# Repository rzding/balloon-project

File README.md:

# SSI high-altitude balloon project

**Firmware:** [`balloon-project-stm32mx/`](balloon-project-stm32mx/) — STM32F411 flight-computer firmware (build, flash, and coding standards).

**Standards and phases:** [`Software Documents/Main Developmental Roadmap.md`](Software%20Documents/Main%20Developmental%20Roadmap.md)

**Verification workflow:** [`Software Documents/Firmware Development Guidelines.md`](Software%20Documents/Firmware%20Development%20Guidelines.md) — deferred hardware, host tests, bench backlog (roadmap §21). Software-complete unblocks the next driver phase; hardware exit is ticked during bring-up week, not before coding the next phase.

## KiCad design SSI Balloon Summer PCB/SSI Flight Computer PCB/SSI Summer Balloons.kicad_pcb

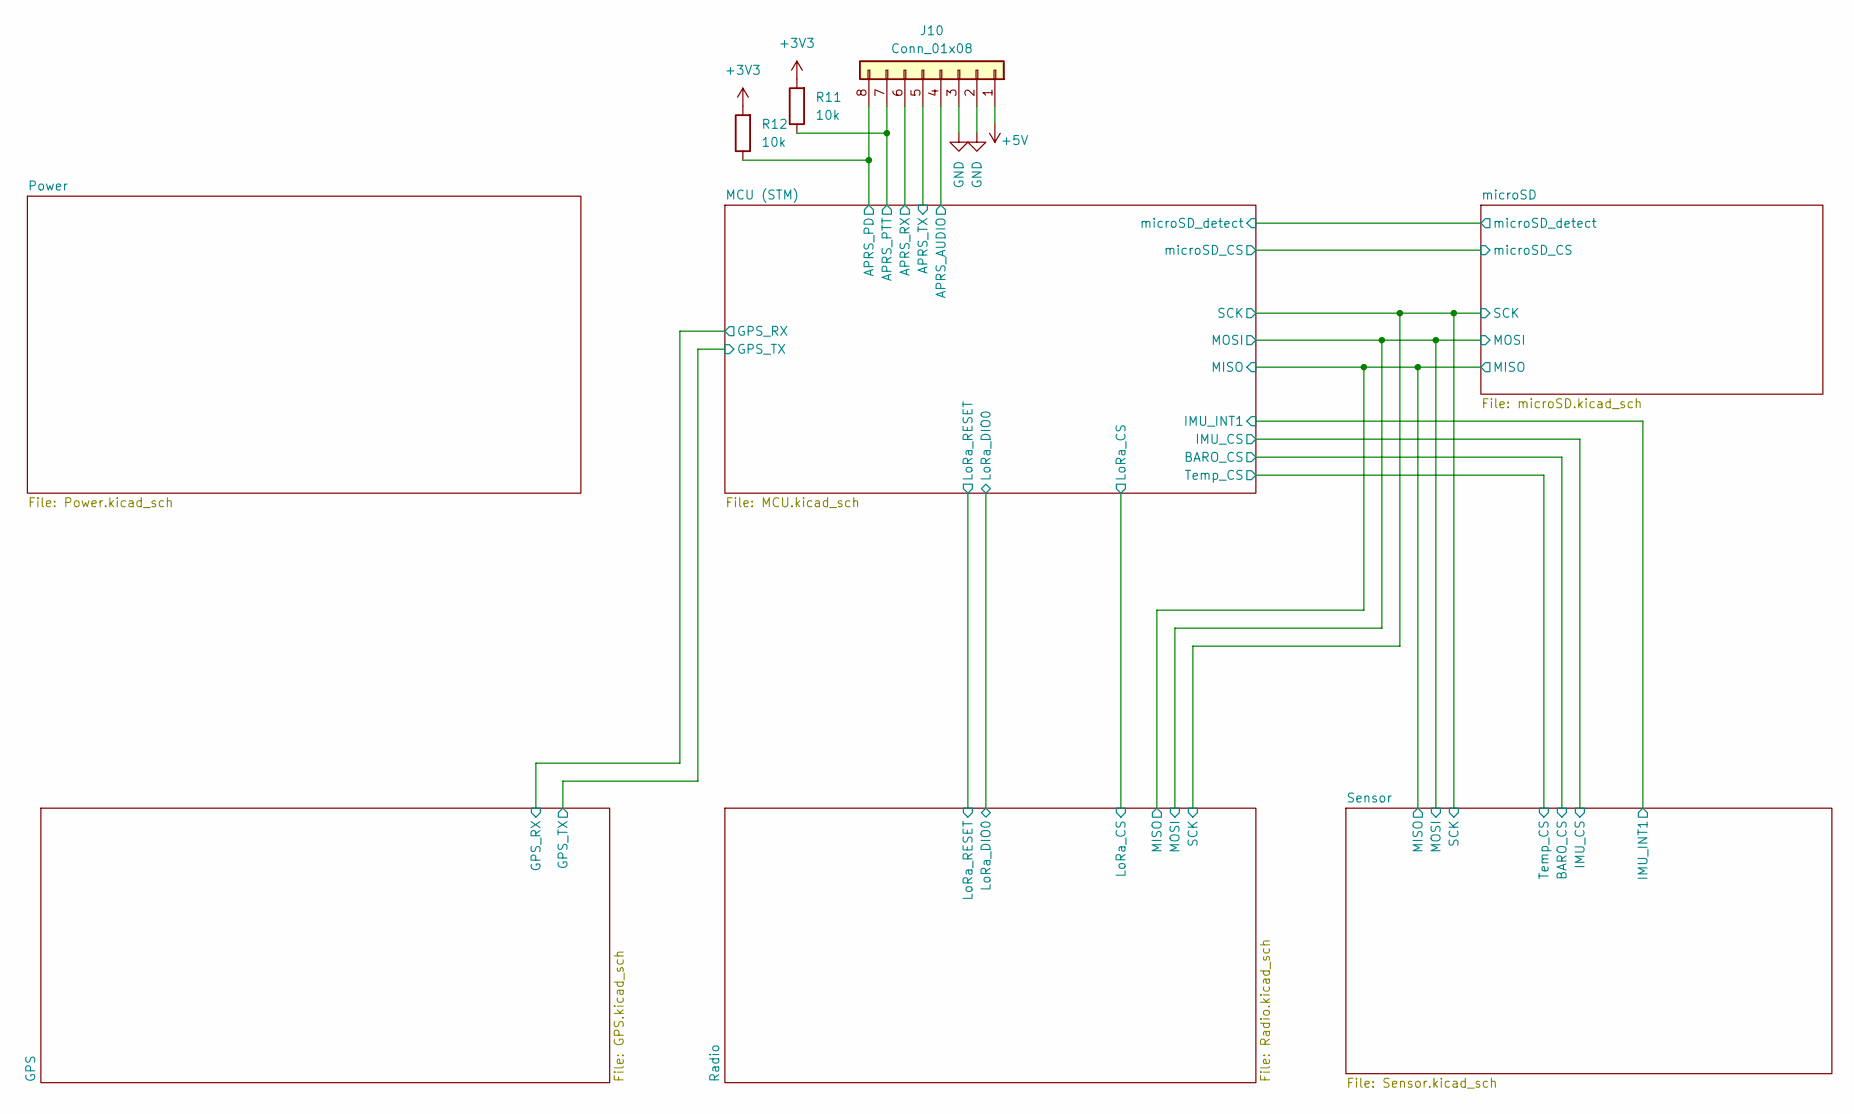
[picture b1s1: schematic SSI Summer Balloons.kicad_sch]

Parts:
J10: Conn_01x08; JST_XH_S8B-XH-A-1_1x08_P2.50mm_Horizontal; LCSC C157914
R11, R12: 10k; R_0603_1608Metric; LCSC C25804

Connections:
+3V3: R11.2, R12.2; also elsewhere on the board
+5V: J10.1; also elsewhere on the board
/MCU (STM)/APRS_AUDIO: J10.4; also elsewhere on the board
/MCU (STM)/APRS_PD: J10.8, R12.1; also elsewhere on the board
/MCU (STM)/APRS_PTT: J10.7, R11.1; also elsewhere on the board
/MCU (STM)/APRS_RX: J10.6; also elsewhere on the board
/MCU (STM)/APRS_TX: J10.5; also elsewhere on the board
GND: J10.2, J10.3; also elsewhere on the board

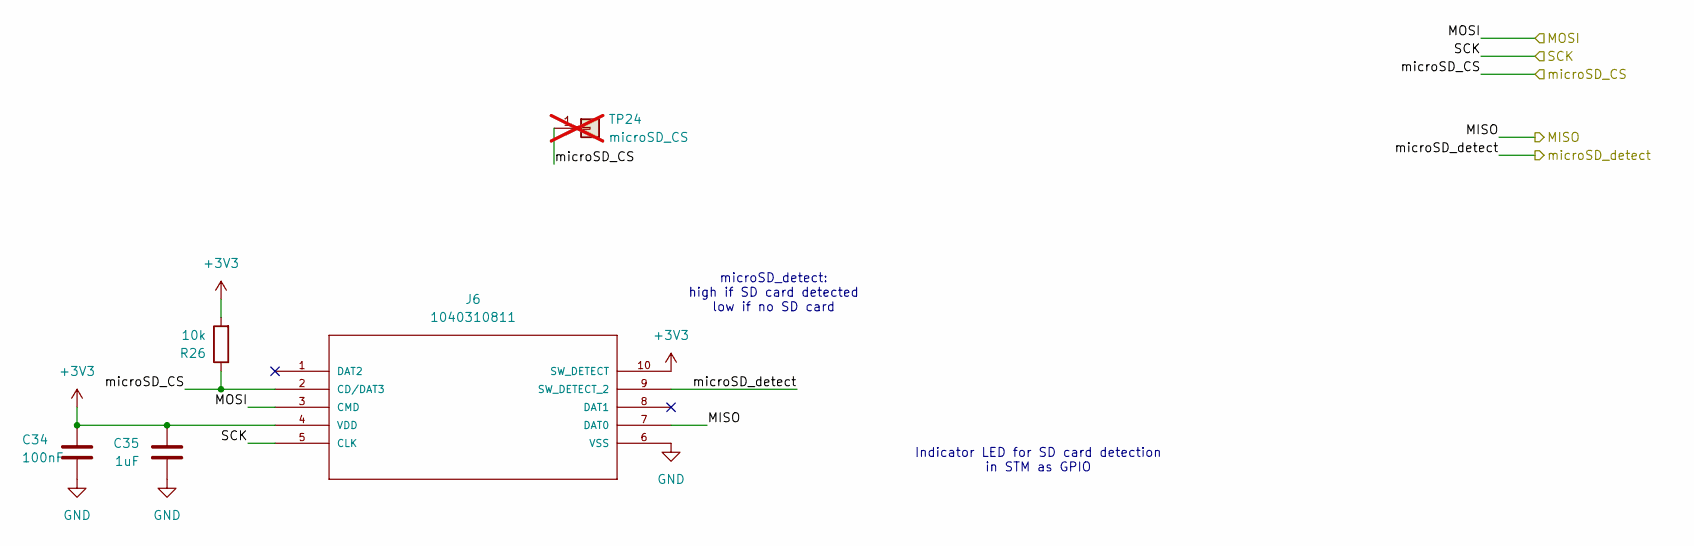
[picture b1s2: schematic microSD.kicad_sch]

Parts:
C34: 100nF; C_0603_1608Metric; LCSC C14663
C35: 1uF; C_0603_1608Metric; LCSC C29936
J6: 1040310811; 104031-0811_MOL; MANUFACTURER_PART_NUMBER 1040310811; LCSC C585350
R26: 10k; R_0603_1608Metric; LCSC C25804
TP24: microSD_CS; PinHeader_1x01_P2.54mm_Vertical; LCSC C81276; not fitted

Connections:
+3V3: C34.1, C35.1, J6.4 (VDD), J6.10 (SW_DETECT), R26.2; also elsewhere on the board
/MCU (STM)/MISO: J6.7 (DAT0); also elsewhere on the board
/MCU (STM)/MOSI: J6.3 (CMD); also elsewhere on the board
/MCU (STM)/SCK: J6.5 (CLK); also elsewhere on the board
/MCU (STM)/microSD_CS: J6.2 (CD/DAT3), R26.1, TP24.1 (Pin_1_1); also elsewhere on the board
/MCU (STM)/microSD_detect: J6.9 (SW_DETECT_2); also elsewhere on the board
GND: C34.2, C35.2, J6.6 (VSS); also elsewhere on the board

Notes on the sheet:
microSD_detect: high if SD card detected low if no SD card
Indicator LED for SD card detection in STM as GPIO

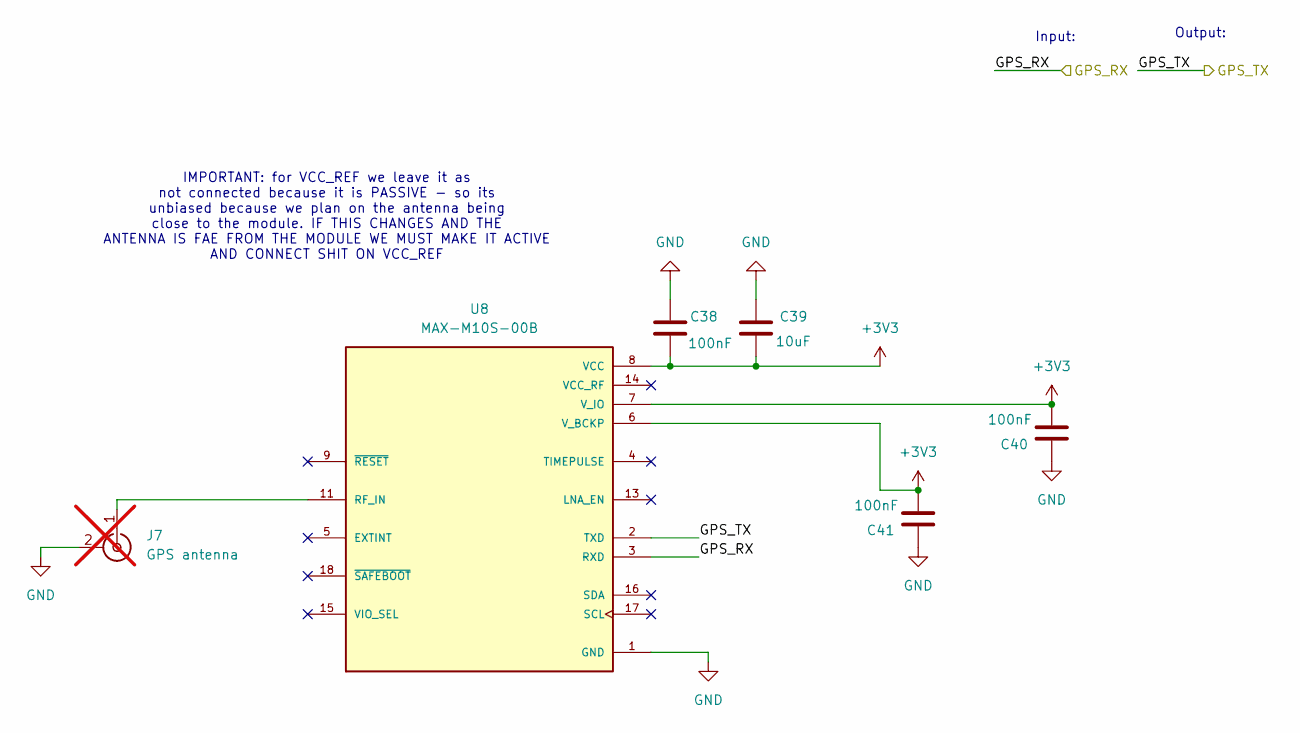
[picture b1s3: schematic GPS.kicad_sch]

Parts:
C38, C40, C41: 100nF; C_0603_1608Metric; LCSC C14663
C39: 10uF; C_0805_2012Metric; LCSC C15850
J7: GPS antenna; SMA_Amphenol_901-144_Vertical; LCSC C376663; not fitted
U8: MAX-M10S-00B; XCVR_MAX-M10S-00B; PARTREV C1; LCSC C4153167

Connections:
+3V3: C38.2, C39.2, C40.2, C41.2, U8.6 (V_BCKP), U8.7 (V_IO), U8.8 (VCC); also elsewhere on the board
GND: C38.1, C39.1, C40.1, C41.1, J7.2 (Ext), U8.1 (GND), U8.10 (GND), U8.12 (GND); also elsewhere on the board
unnamed 40: J7.1 (In), U8.11 (RF_IN); also elsewhere on the board

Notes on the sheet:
IMPORTANT: for VCC_REF we leave it as not connected because it is PASSIVE - so its unbiased because we plan on the antenna being close to the module. IF THIS CHANGES AND THE ANTENNA IS FAE FROM THE MODULE WE MUST MAKE IT ACTIVE AND CONNECT SHIT ON VCC_REF
Output:
Input:

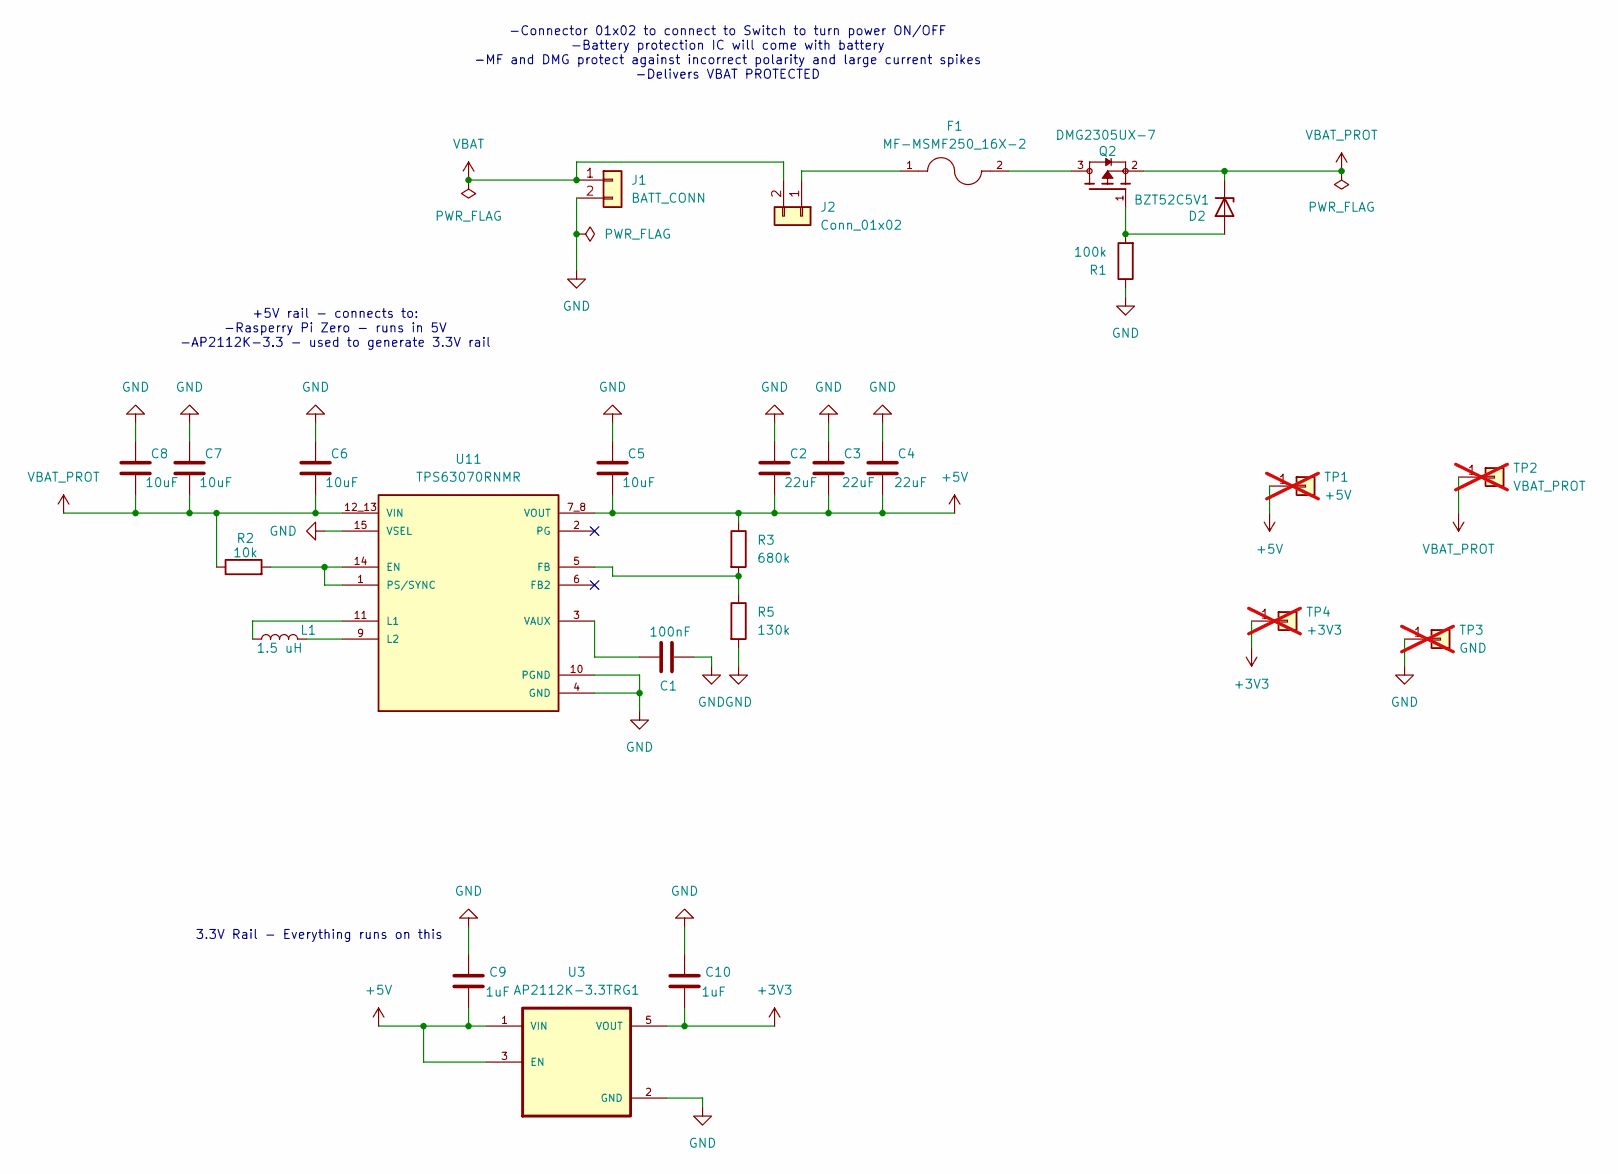
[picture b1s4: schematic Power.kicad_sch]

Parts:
C1: 100nF; C_0603_1608Metric; LCSC C14663
C2, C3, C4: 22uF; C_0805_2012Metric; LCSC C45783
C5, C6: 10uF; C_0603_1608Metric; LCSC C96446
C7, C8: 10uF; C_0805_2012Metric; LCSC C15850
C9, C10: 1uF; C_0603_1608Metric; LCSC C29936
D2: BZT52C5V1; D_SOD-123; LCSC C2117
F1: MF-MSMF250_16X-2; FUSER_MF-MSMF250_16X-2; LCSC C210838
J1: BATT_CONN; JST_XH_B2B-XH-A_1x02_P2.50mm_Vertical; LCSC C265283
J2: Conn_01x02; JST_XH_B2B-XH-A_1x02_P2.50mm_Vertical; LCSC C265283
L1: 1.5 uH; L_Coilcraft_XxL4020; LCSC C18547833
Q2: DMG2305UX-7; SOT91P240X110-3N_DMG2305UX-7; PARTREV 09/2018; LCSC C5261054
R1: 100k; R_0603_1608Metric; LCSC C25803
R2: 10k; R_0603_1608Metric; LCSC C25804
R3: 680k; R_0603_1608Metric; LCSC C25822
R5: 130k; R_0603_1608Metric; LCSC C22795
TP1: +5V; PinHeader_1x01_P2.54mm_Vertical; LCSC C81276; not fitted
TP2: VBAT_PROT; PinHeader_1x01_P2.54mm_Vertical; LCSC C81276; not fitted
TP3: GND; PinHeader_1x01_P2.54mm_Vertical; LCSC C81276; not fitted
TP4: +3V3; PinHeader_1x01_P2.54mm_Vertical; LCSC C81276; not fitted
U3: AP2112K-3.3TRG1; SOT95P285X140-5N; PARTREV 2-2; LCSC C51118
U11: TPS63070RNMR; VREG_TPS63070RNMR; PARTREV B; LCSC C109322

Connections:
+3V3: C10.2, TP4.1 (Pin_1_1), U3.5 (VOUT); also elsewhere on the board
+5V: C2.2, C3.2, C4.2, C5.2, C9.2, R3.1, TP1.1 (Pin_1_1), U3.1 (VIN), U3.3 (EN), U11.7_8 (VOUT); also elsewhere on the board
GND: C1.2, C2.1, C3.1, C4.1, C5.1, C6.1, C7.1, C8.1, C9.1, C10.1, J1.2, R1.1, R5.2, TP3.1 (Pin_1_1), U3.2 (GND), U11.4 (GND), U11.10 (PGND), U11.15 (VSEL); also elsewhere on the board
unnamed: D2.2 (A), Q2.1, R1.2
unnamed: F1.2, Q2.3
unnamed: F1.1, J2.1
unnamed: R2.2, U11.1 (PS/SYNC), U11.14 (EN)
unnamed: R3.2, R5.1, U11.5 (FB)
unnamed: L1.1, U11.11 (L1)
unnamed: L1.2, U11.9 (L2)
unnamed: C1.1, U11.3 (VAUX)
VBAT: J1.1, J2.2
VBAT_PROT: C6.2, C7.2, C8.2, D2.1 (K), Q2.2, R2.1, TP2.1 (Pin_1_1), U11.12_13 (VIN)

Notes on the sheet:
-Connector 01x02 to connect to Switch to turn power ON/OFF -Battery protection IC will come with battery -MF and DMG protect against incorrect polarity and large current spikes -Delivers VBAT PROTECTED
3.3V Rail - Everything runs on this
+5V rail - connects to: -Rasperry Pi Zero - runs in 5V -AP2112K-3.3 - used to generate 3.3V rail

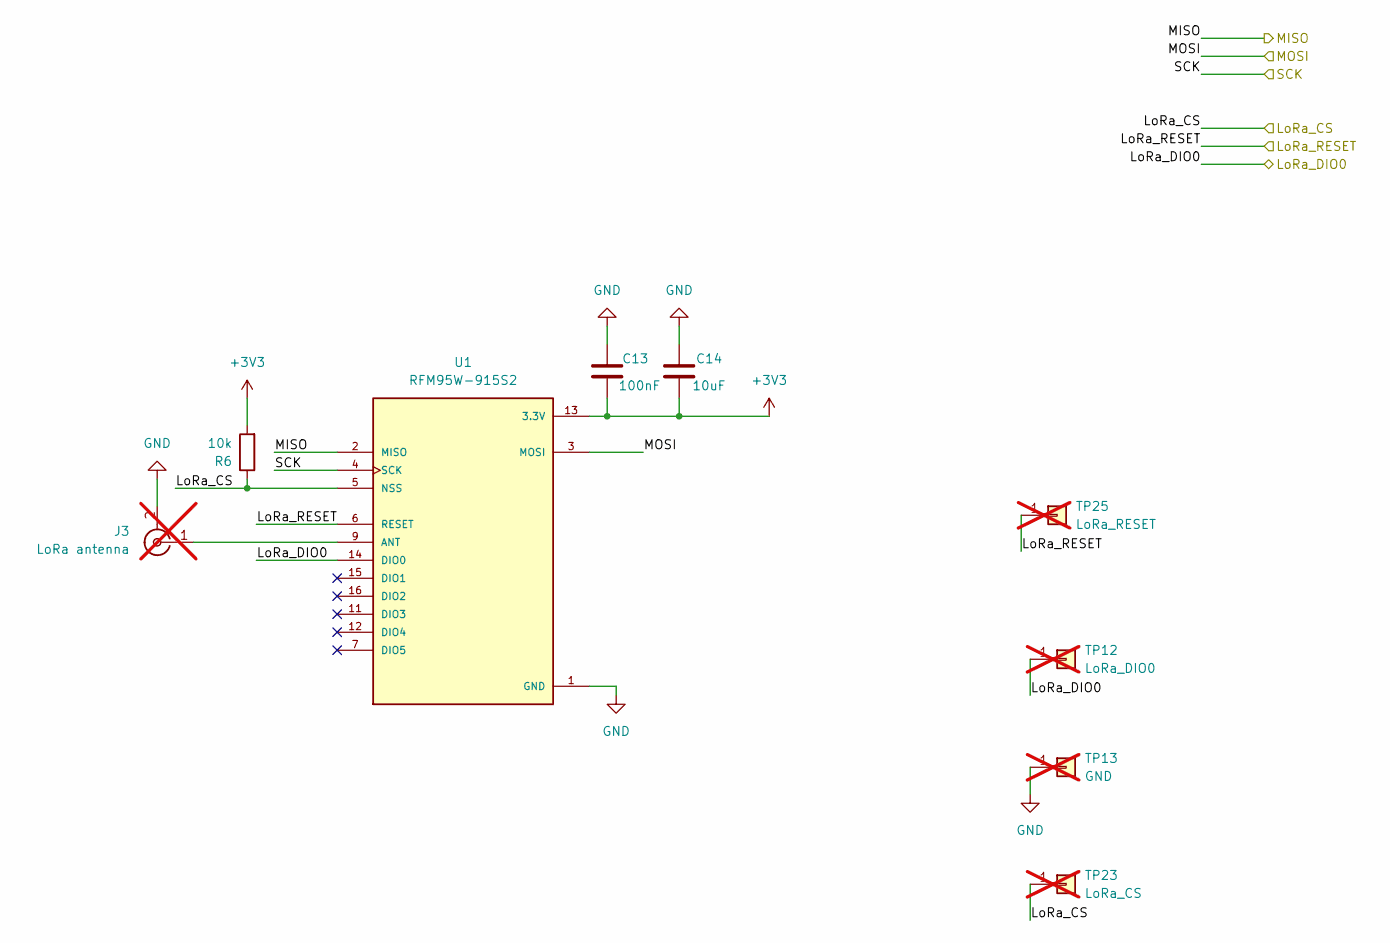
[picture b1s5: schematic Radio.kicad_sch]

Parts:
C13: 100nF; C_0603_1608Metric; LCSC C14663
C14: 10uF; C_0805_2012Metric; LCSC C15850
J3: LoRa antenna; SMA_Amphenol_901-144_Vertical; LCSC C376663; not fitted
R6: 10k; R_0603_1608Metric; LCSC C25804
TP12: LoRa_DIO0; PinHeader_1x01_P2.54mm_Vertical; LCSC C81276; not fitted
TP13: GND; PinHeader_1x01_P2.54mm_Vertical; LCSC C81276; not fitted
TP23: LoRa_CS; PinHeader_1x01_P2.54mm_Vertical; LCSC C81276; not fitted
TP25: LoRa_RESET; PinHeader_1x01_P2.54mm_Vertical; LCSC C81276; not fitted
U1: RFM95W-915S2; XCVR_RFM95W-915S2; LCSC C2844473

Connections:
+3V3: C13.2, C14.2, R6.2, U1.13 (3.3V); also elsewhere on the board
/MCU (STM)/LoRa_CS: R6.1, TP23.1 (Pin_1_1), U1.5 (NSS); also elsewhere on the board
/MCU (STM)/LoRa_DIO0: TP12.1 (Pin_1_1), U1.14 (DIO0); also elsewhere on the board
/MCU (STM)/LoRa_RESET: TP25.1 (Pin_1_1), U1.6 (RESET); also elsewhere on the board
GND: C13.1, C14.1, J3.2 (Ext), TP13.1 (Pin_1_1), U1.1 (GND), U1.8 (GND), U1.10 (GND); also elsewhere on the board
unnamed 39: J3.1 (In), U1.9 (ANT); also elsewhere on the board

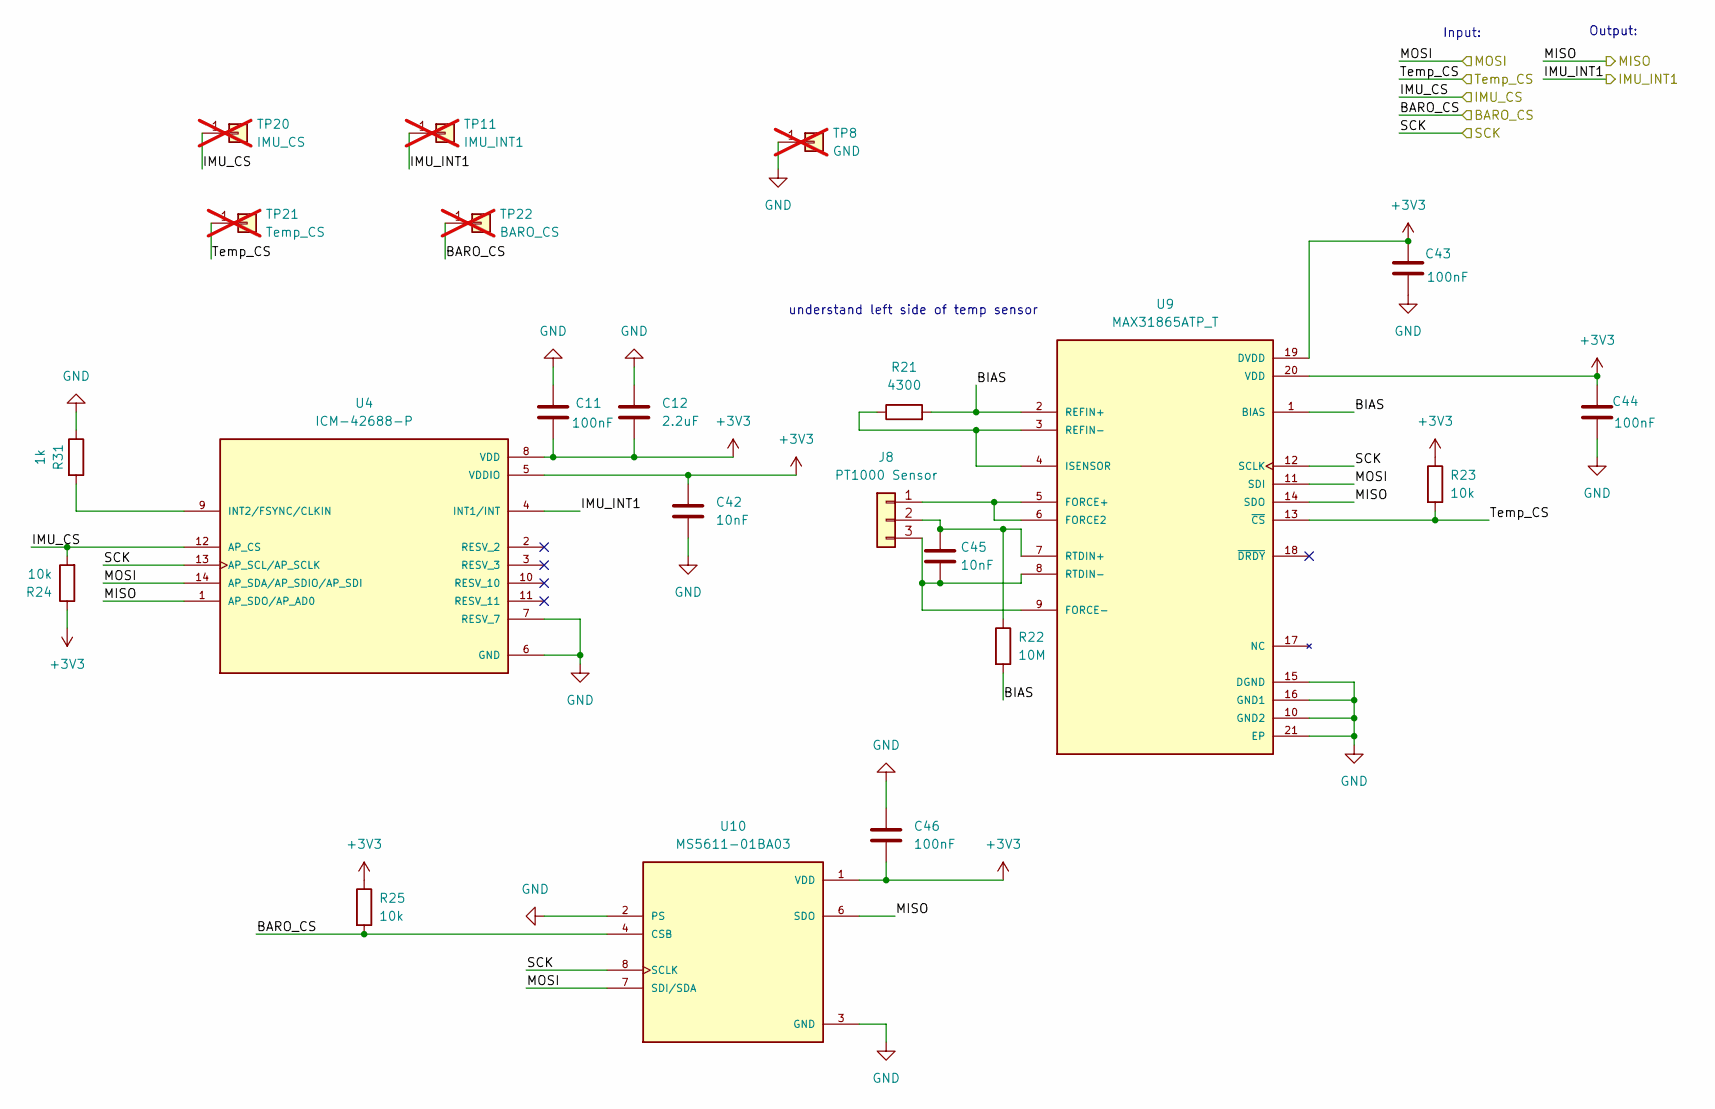
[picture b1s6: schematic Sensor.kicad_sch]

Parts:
C11, C43, C44, C46: 100nF; C_0603_1608Metric; LCSC C14663
C12: 2.2uF; C_0603_1608Metric; LCSC C43922
C42, C45: 10nF; C_0603_1608Metric; LCSC C57112
J8: PT1000 Sensor; JST_PH_B3B-PH-K_1x03_P2.00mm_Vertical; LCSC C158004
R21: 4300; R_0603_1608Metric; LCSC C2989227
R22: 10M; R_0603_1608Metric; LCSC C7250
R23, R24, R25: 10k; R_0603_1608Metric; LCSC C25804
R31: 1k; R_0603_1608Metric; LCSC C21190
TP8: GND; PinHeader_1x01_P2.54mm_Vertical; LCSC C81276; not fitted
TP11: IMU_INT1; PinHeader_1x01_P2.54mm_Vertical; LCSC C81276; not fitted
TP20: IMU_CS; PinHeader_1x01_P2.54mm_Vertical; LCSC C81276; not fitted
TP21: Temp_CS; PinHeader_1x01_P2.54mm_Vertical; LCSC C81276; not fitted
TP22: BARO_CS; PinHeader_1x01_P2.54mm_Vertical; LCSC C81276; not fitted
U4: ICM-42688-P; PQFN50P300X250X97-14N; PARTREV 1.2; LCSC C1850418
U9: MAX31865ATP_T; QFN65P500X500X80-21N; PARTREV 3; LCSC C118474
U10: MS5611-01BA03; SON125P500X300X100-8N; PARTREV 06/2017; LCSC C15639

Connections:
+3V3: C11.2, C12.2, C42.1, C43.1, C44.1, C46.2, R23.1, R24.1, R25.1, U4.5 (VDDIO), U4.8 (VDD), U9.19 (DVDD), U9.20 (VDD), U10.1 (VDD); also elsewhere on the board
/MCU (STM)/BARO_CS: R25.2, TP22.1 (Pin_1_1), U10.4 (CSB), U10.5 (CSB); also elsewhere on the board
/MCU (STM)/IMU_CS: R24.2, TP20.1 (Pin_1_1), U4.12 (AP_CS); also elsewhere on the board
/MCU (STM)/IMU_INT1: TP11.1 (Pin_1_1), U4.4 (INT1/INT); also elsewhere on the board
/MCU (STM)/MISO: U4.1 (AP_SDO/AP_AD0), U9.14 (SDO), U10.6 (SDO); also elsewhere on the board
/MCU (STM)/MOSI: U4.14 (AP_SDA/AP_SDIO/AP_SDI), U9.11 (SDI), U10.7 (SDI/SDA); also elsewhere on the board
/MCU (STM)/SCK: U4.13 (AP_SCL/AP_SCLK), U9.12 (SCLK), U10.8 (SCLK); also elsewhere on the board
/MCU (STM)/Temp_CS: R23.2, TP21.1 (Pin_1_1), U9.13 (~CS); also elsewhere on the board
/Sensor/BIAS: R21.2, R22.2, U9.1 (BIAS), U9.2 (REFIN+)
GND: C11.1, C12.1, C42.2, C43.2, C44.2, C46.1, R31.1, TP8.1 (Pin_1_1), U4.6 (GND), U4.7 (RESV_7), U9.10 (GND2), U9.15 (DGND), U9.16 (GND1), U9.21 (EP), U10.2 (PS), U10.3 (GND); also elsewhere on the board
unnamed: J8.1, U9.5 (FORCE+), U9.6 (FORCE2)
unnamed: C45.1, J8.2, R22.1, U9.7 (RTDIN+)
unnamed: C45.2, J8.3, U9.8 (RTDIN-), U9.9 (FORCE-)
unnamed: R31.2, U4.9 (INT2/FSYNC/CLKIN)
unnamed: R21.1, U9.3 (REFIN-), U9.4 (ISENSOR)

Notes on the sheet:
Output:
understand left side of temp sensor
Input:

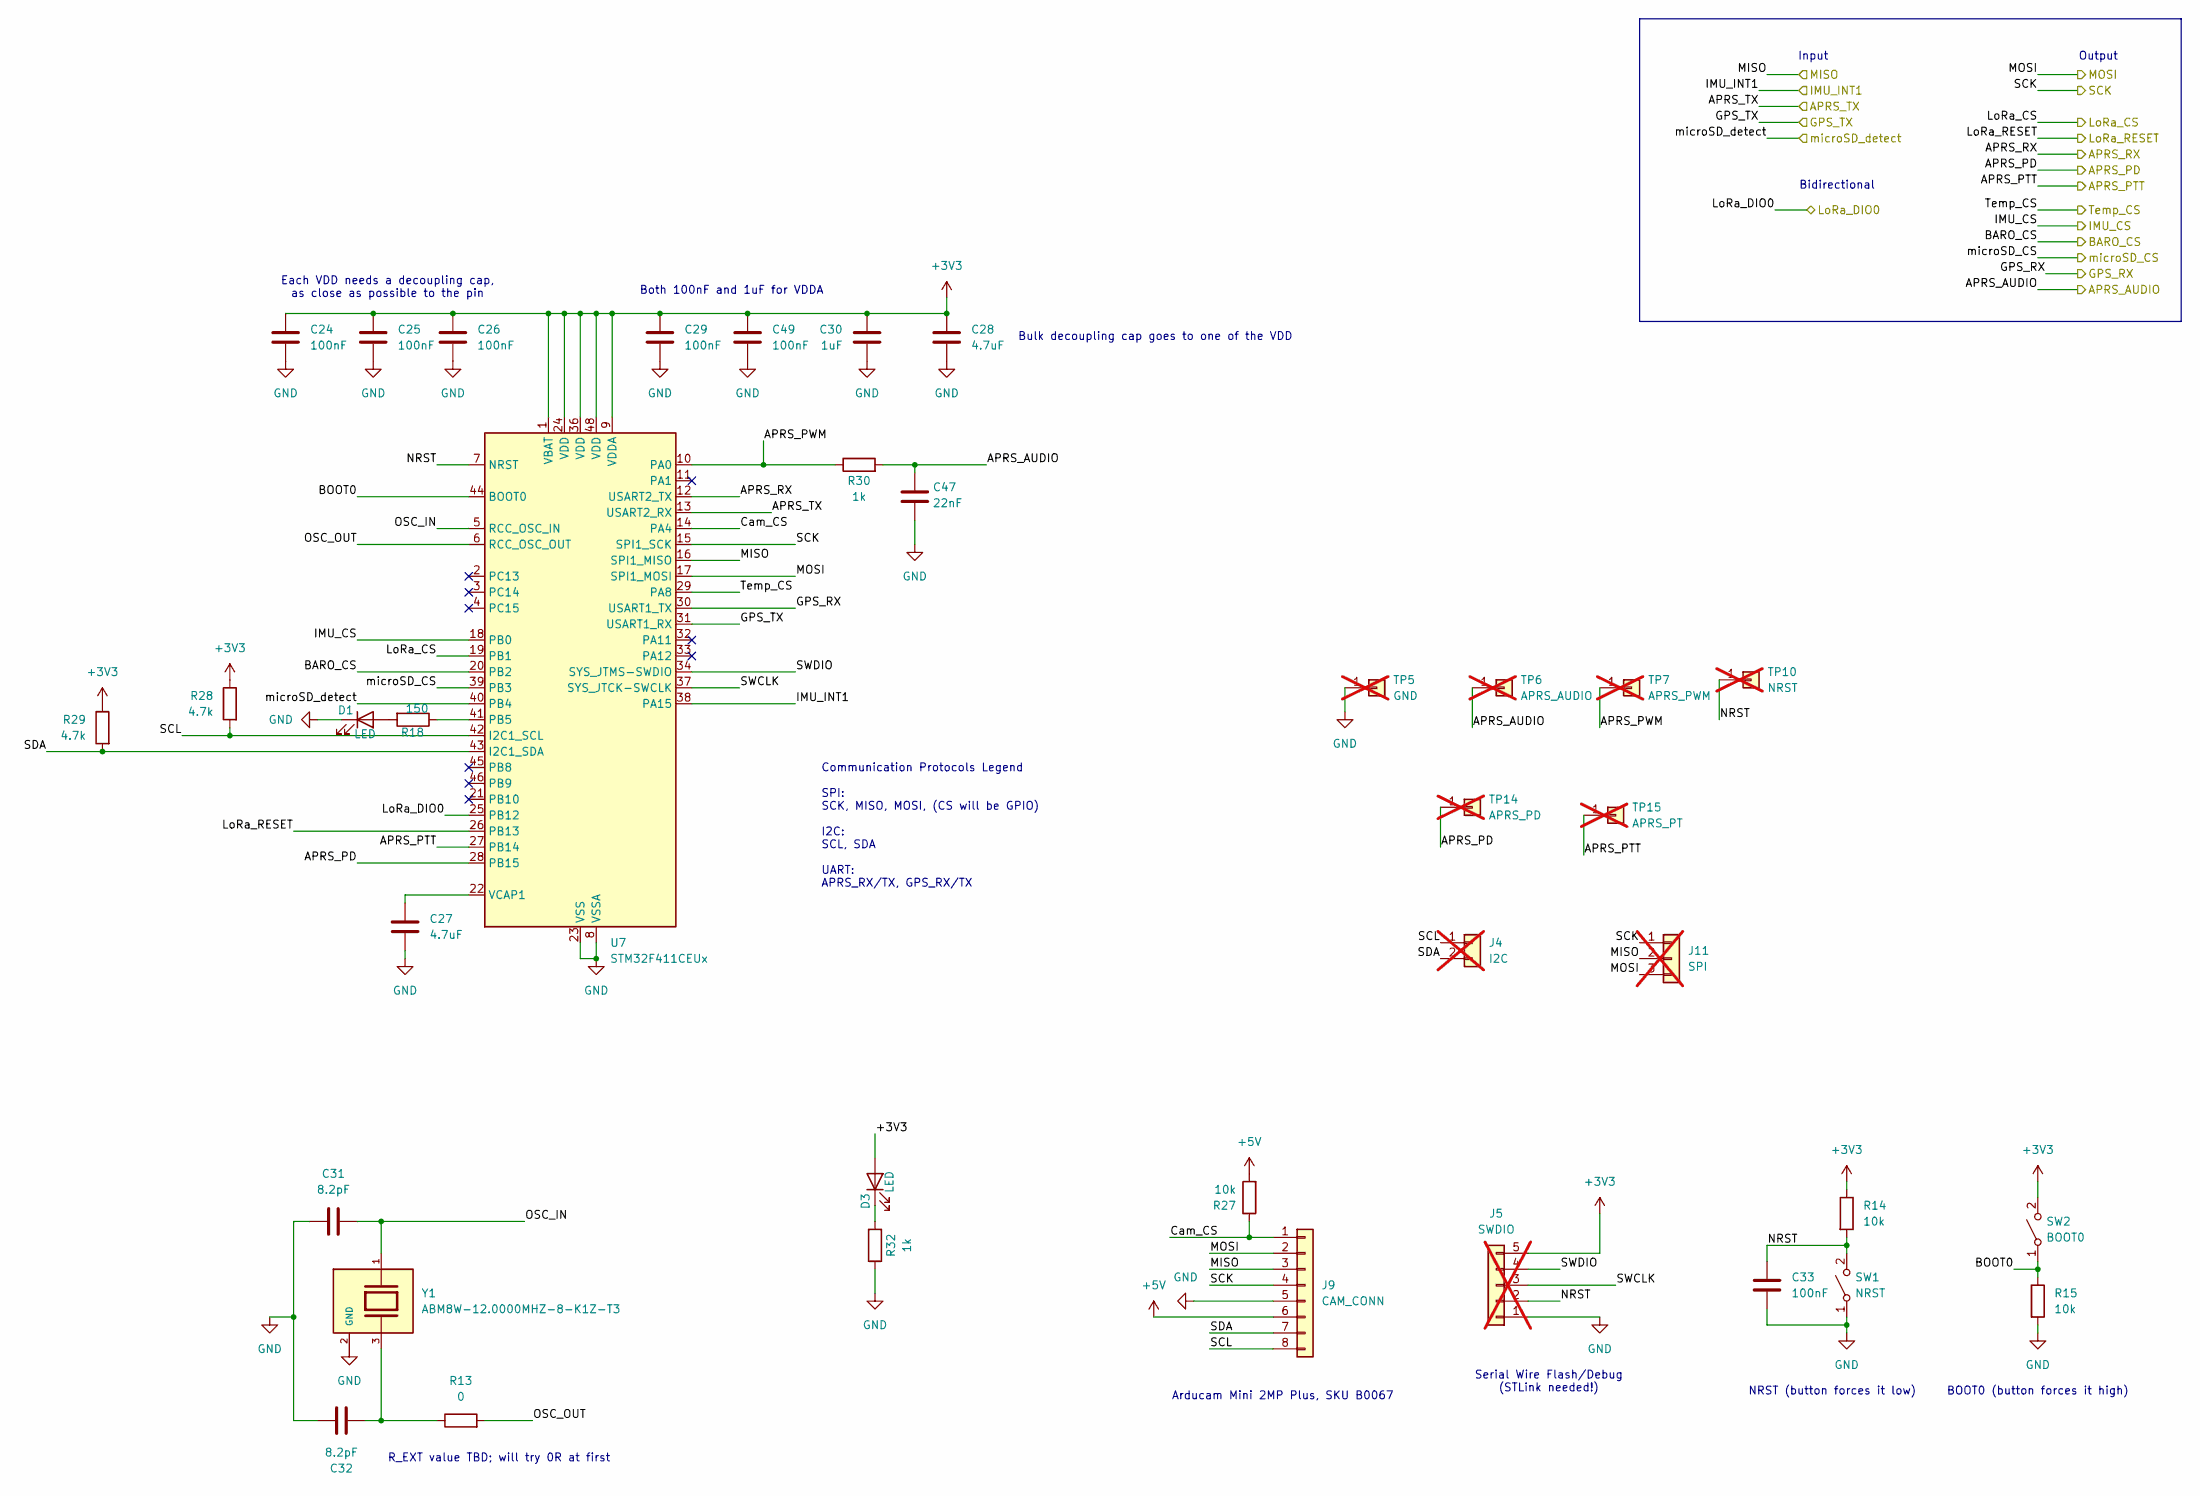
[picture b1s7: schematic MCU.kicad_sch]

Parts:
C24, C25, C26, C29, C33, C49: 100nF; C_0603_1608Metric; LCSC C14663
C27, C28: 4.7uF; C_0805_2012Metric; LCSC C76639
C30: 1uF; C_0603_1608Metric; LCSC C29936
C31, C32: 8.2pF; C_0603_1608Metric; LCSC C1685
C47: 22nF; C_0603_1608Metric; LCSC C49326627
D1: LED; LED_0805_2012Metric; LCSC C2297
D3: LED; LED_0805_2012Metric; LCSC C84256
J4: I2C; PinHeader_1x02_P2.54mm_Vertical; LCSC C168673; not fitted
J5: SWDIO; PinHeader_1x05_P2.54mm_Vertical; LCSC C5156614; not fitted
J9: CAM_CONN; JST_XH_B8B-XH-A_1x08_P2.50mm_Vertical; LCSC C161875
J11: SPI; PinHeader_1x03_P2.54mm_Vertical; LCSC C49257; not fitted
R13: 0; R_0603_1608Metric; LCSC C21189
R14, R15, R27: 10k; R_0603_1608Metric; LCSC C25804
R18: 150; R_0603_1608Metric; LCSC C22808
R28, R29: 4.7k; R_0603_1608Metric; LCSC C98195
R30, R32: 1k; R_0603_1608Metric; LCSC C21190
SW1: NRST; SW_SPST_B3U-1000P; LCSC C720477
SW2: BOOT0; SW_SPST_B3U-1000P; LCSC C720477
TP5: GND; PinHeader_1x01_P2.54mm_Vertical; LCSC C81276; not fitted
TP6: APRS_AUDIO; PinHeader_1x01_P2.54mm_Vertical; LCSC C81276; not fitted
TP7: APRS_PWM; PinHeader_1x01_P2.54mm_Vertical; LCSC C81276; not fitted
TP10: NRST; PinHeader_1x01_P2.54mm_Vertical; LCSC C81276; not fitted
TP14: APRS_PD; PinHeader_1x01_P2.54mm_Vertical; LCSC C81276; not fitted
TP15: APRS_PT; PinHeader_1x01_P2.54mm_Vertical; LCSC C81276; not fitted
U7: STM32F411CEUx; QFN-48-1EP_7x7mm_P0.5mm_EP5.6x5.6mm; LCSC C60420
Y1: ABM8W-12.0000MHZ-8-K1Z-T3; XTAL_ABM8W-12.0000MHZ-8-K1Z-T3; PARTREV 08.09.2018; DigiKey_Part_Number 535-14010-1-ND

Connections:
+3V3: C24.1, C25.1, C26.1, C28.1, C29.1, C30.1, C49.1, D3.2 (A), J5.5, R14.1, R28.1, R29.1, SW2.2 (B), U7.1 (VBAT), U7.9 (VDDA), U7.24 (VDD), U7.36 (VDD), U7.48 (VDD); also elsewhere on the board
+5V: J9.6, R27.2; also elsewhere on the board
/GPS/GPS_RX: U7.30 (USART1_TX); also elsewhere on the board
/GPS/GPS_TX: U7.31 (USART1_RX); also elsewhere on the board
/MCU (STM)/APRS_AUDIO: C47.1, R30.2, TP6.1 (Pin_1_1); also elsewhere on the board
/MCU (STM)/APRS_PD: TP14.1 (Pin_1_1), U7.28 (PB15); also elsewhere on the board
/MCU (STM)/APRS_PTT: TP15.1 (Pin_1_1), U7.27 (PB14); also elsewhere on the board
/MCU (STM)/APRS_PWM: R30.1, TP7.1 (Pin_1_1), U7.10 (PA0)
/MCU (STM)/APRS_RX: U7.12 (USART2_TX); also elsewhere on the board
/MCU (STM)/APRS_TX: U7.13 (USART2_RX); also elsewhere on the board
/MCU (STM)/BARO_CS: U7.20 (PB2); also elsewhere on the board
/MCU (STM)/BOOT0: R15.1, SW2.1 (A), U7.44 (BOOT0); also elsewhere on the board
/MCU (STM)/Cam_CS: J9.1, R27.1, U7.14 (PA4)
/MCU (STM)/IMU_CS: U7.18 (PB0); also elsewhere on the board
/MCU (STM)/IMU_INT1: U7.38 (PA15); also elsewhere on the board
/MCU (STM)/LoRa_CS: U7.19 (PB1); also elsewhere on the board
/MCU (STM)/LoRa_DIO0: U7.25 (PB12); also elsewhere on the board
/MCU (STM)/LoRa_RESET: U7.26 (PB13); also elsewhere on the board
/MCU (STM)/MISO: J9.3, J11.2, U7.16 (SPI1_MISO); also elsewhere on the board
/MCU (STM)/MOSI: J9.2, J11.3, U7.17 (SPI1_MOSI); also elsewhere on the board
/MCU (STM)/NRST: C33.1, J5.2, R14.2, SW1.2 (B), TP10.1 (Pin_1_1), U7.7 (NRST); also elsewhere on the board
/MCU (STM)/OSC_IN: C31.2, U7.5 (RCC_OSC_IN), Y1.1
/MCU (STM)/OSC_OUT: R13.2, U7.6 (RCC_OSC_OUT)
/MCU (STM)/SCK: J9.4, J11.1, U7.15 (SPI1_SCK); also elsewhere on the board
/MCU (STM)/SCL: J4.1, J9.8, R28.2, U7.42 (I2C1_SCL)
/MCU (STM)/SDA: J4.2, J9.7, R29.2, U7.43 (I2C1_SDA)
/MCU (STM)/SWCLK: J5.3, U7.37 (SYS_JTCK-SWCLK)
/MCU (STM)/SWDIO: J5.4, U7.34 (SYS_JTMS-SWDIO)
/MCU (STM)/Temp_CS: U7.29 (PA8); also elsewhere on the board
/MCU (STM)/microSD_CS: U7.39 (PB3); also elsewhere on the board
/MCU (STM)/microSD_detect: U7.40 (PB4); also elsewhere on the board
GND: C24.2, C25.2, C26.2, C27.2, C28.2, C29.2, C30.2, C31.1, C32.1, C33.2, C47.2, C49.2, D1.1 (K), J5.1, J9.5, R15.2, R32.1, SW1.1 (A), TP5.1 (Pin_1_1), U7.8 (VSSA), U7.23 (VSS), U7.35 (VSS), U7.47 (VSS), U7.49 (VSS), Y1.2 (GND), Y1.4 (GND); also elsewhere on the board
unnamed: C32.2, R13.1, Y1.3
unnamed: D1.2 (A), R18.2
unnamed: D3.1 (K), R32.2
unnamed: R18.1, U7.41 (PB5)
unnamed: C27.1, U7.22 (VCAP1)

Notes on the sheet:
Bidirectional
NRST (button forces it low)
BOOT0 (button forces it high)
Output
Input
Communication Protocols Legend SPI: SCK, MISO, MOSI, (CS will be GPIO) I2C: SCL, SDA UART: APRS_RX/TX, GPS_RX/TX
R_EXT value TBD; will try 0R at first
Both 100nF and 1uF for VDDA
Each VDD needs a decoupling cap, as close as possible to the pin
Arducam Mini 2MP Plus, SKU B0067
Serial Wire Flash/Debug (STLink needed!)
Bulk decoupling cap goes to one of the VDD

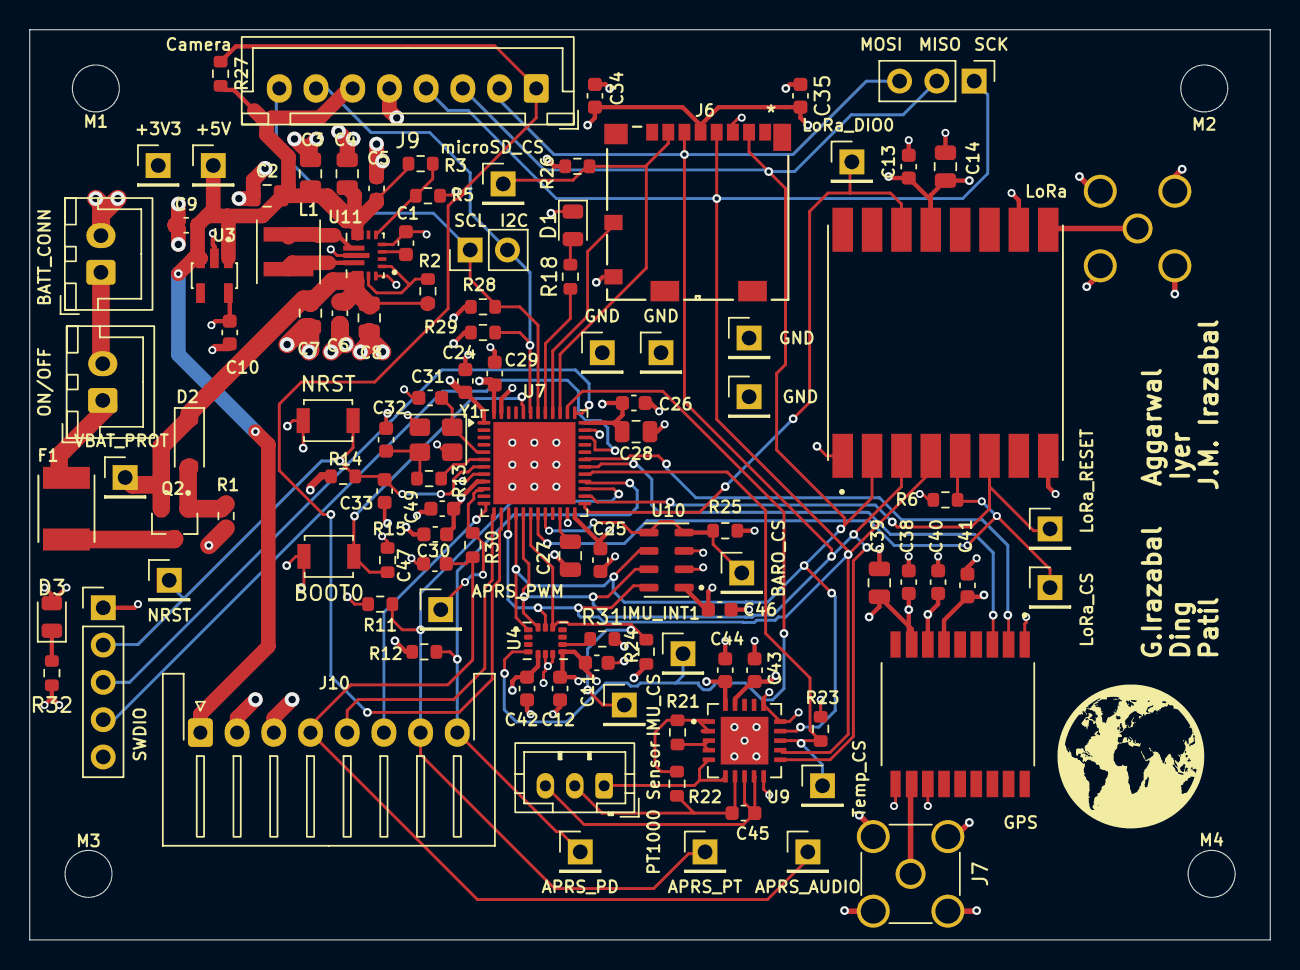
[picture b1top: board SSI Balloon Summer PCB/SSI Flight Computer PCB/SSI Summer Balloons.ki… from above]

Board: 4 copper layers, 84.5 x 62.0 mm, 112 parts (1 on the bottom side), 55 nets.

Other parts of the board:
BOOT0: BOOT0; SW_SPST_B3U-1000P
GPS: MAX-M10S-00B; XCVR_MAX-M10S-00B
LoRa: RFM95W-915S2; XCVR_RFM95W-915S2
M1, M2, M3, M4: MountingHole_3.2mm_M3
NRST: NRST; SW_SPST_B3U-1000P

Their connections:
+3V3: BOOT0.2 (B), GPS.6 (V_BCKP), GPS.7 (V_IO), GPS.8 (VCC), LoRa.13 (3.3V); also elsewhere on the board
/GPS/GPS_RX: GPS.3 (RXD); also elsewhere on the board
/GPS/GPS_TX: GPS.2 (TXD); also elsewhere on the board
/MCU (STM)/BOOT0: BOOT0.1 (A); also elsewhere on the board
/MCU (STM)/LoRa_CS: LoRa.5 (NSS); also elsewhere on the board
/MCU (STM)/LoRa_DIO0: LoRa.14 (DIO0); also elsewhere on the board
/MCU (STM)/LoRa_RESET: LoRa.6 (RESET); also elsewhere on the board
/MCU (STM)/MISO: LoRa.2 (MISO); also elsewhere on the board
/MCU (STM)/MOSI: LoRa.3 (MOSI); also elsewhere on the board
/MCU (STM)/NRST: NRST.2 (B); also elsewhere on the board
/MCU (STM)/SCK: LoRa.4 (SCK); also elsewhere on the board
GND: GPS.1 (GND), GPS.10 (GND), GPS.12 (GND), LoRa.1 (GND), LoRa.8 (GND), LoRa.10 (GND), NRST.1 (A); also elsewhere on the board
unnamed 39: LoRa.9 (ANT); also elsewhere on the board
unnamed 40: GPS.11 (RF_IN); also elsewhere on the board
